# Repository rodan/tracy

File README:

gps tracker based on a MSP430F5510 uC with a gprs connection for reporting and command input.

 source:       https://github.com/rodan/tracy 
 author:       Petre Rodan <2b4eda@subdimension.ro>
 license:      GNU GPLv3

Features:
 - both hardware and software are opensource
 - an f-ram chip for input data buffering
 - resilient software architecture
 - all gps/gsm operations controlled by timer interrupts which allows control of both sub-systems in the same time
 - great flexibility given by configuration variables

 prototype pictures available here:  https://photos.app.goo.gl/5ZgdGM5Km6QHHfX5A
 documentation available here:       https://github.com/rodan/tracy/blob/master/doc/tracy_manual.pdf

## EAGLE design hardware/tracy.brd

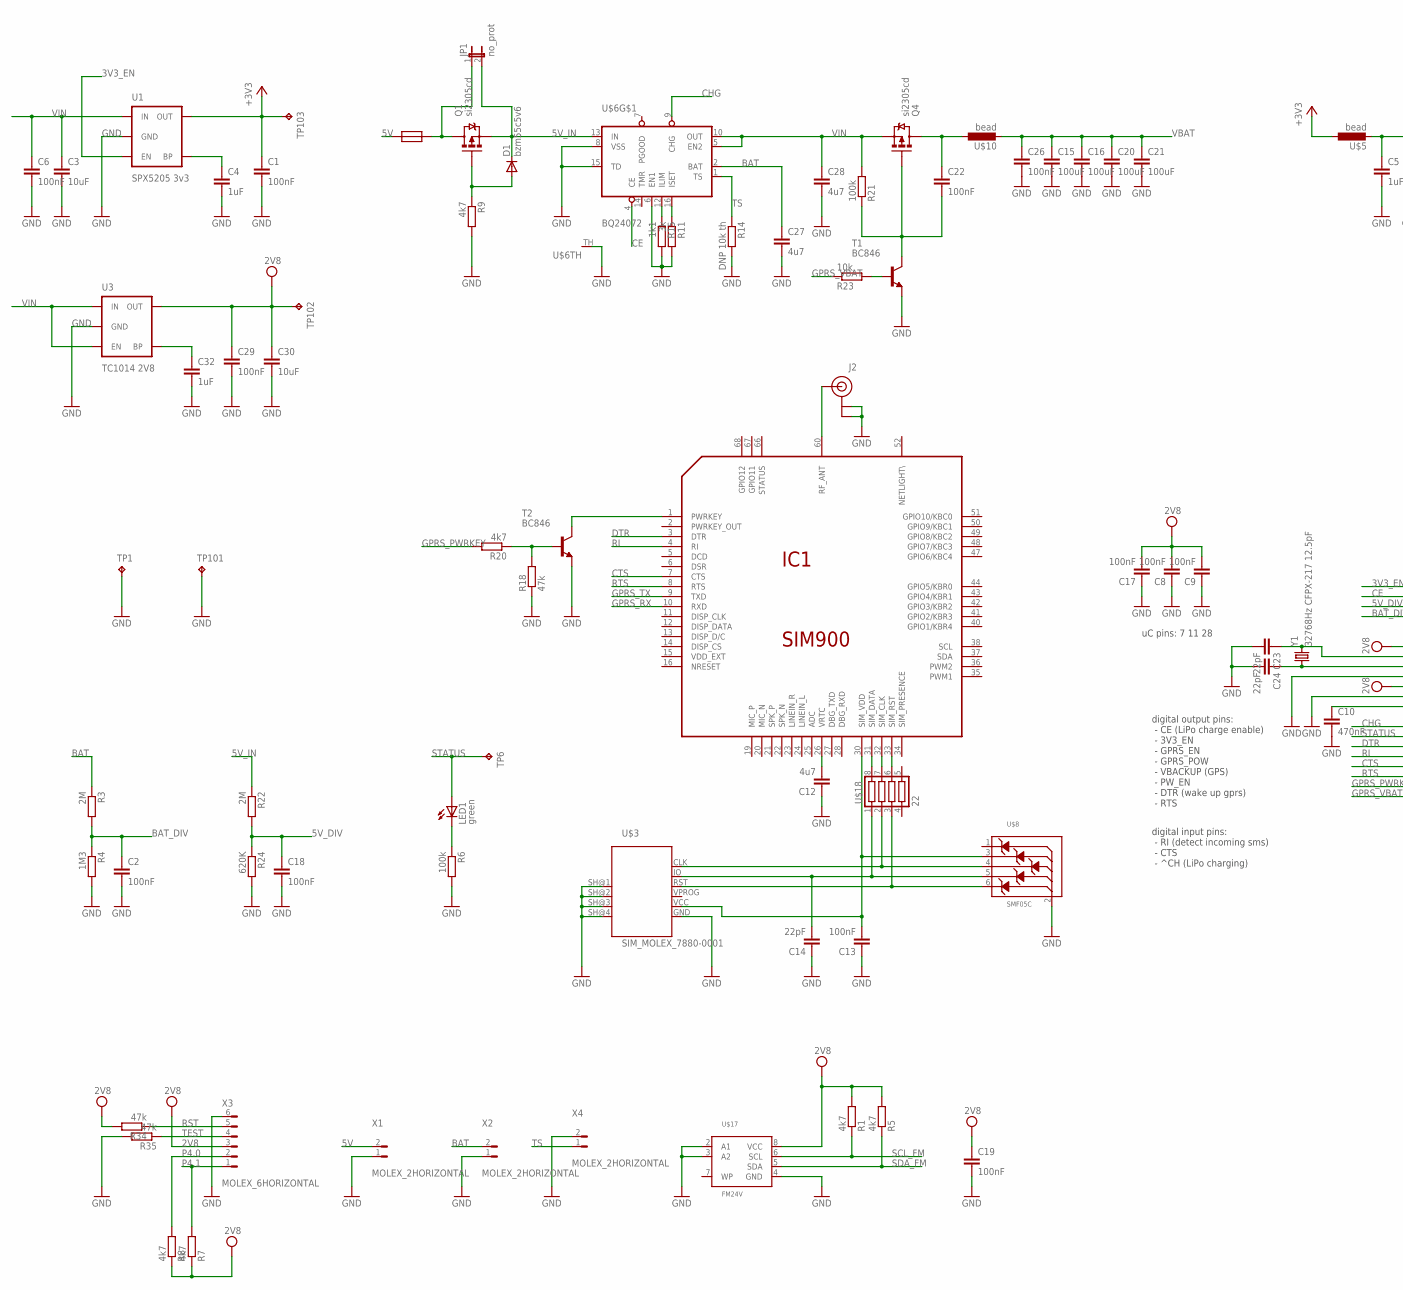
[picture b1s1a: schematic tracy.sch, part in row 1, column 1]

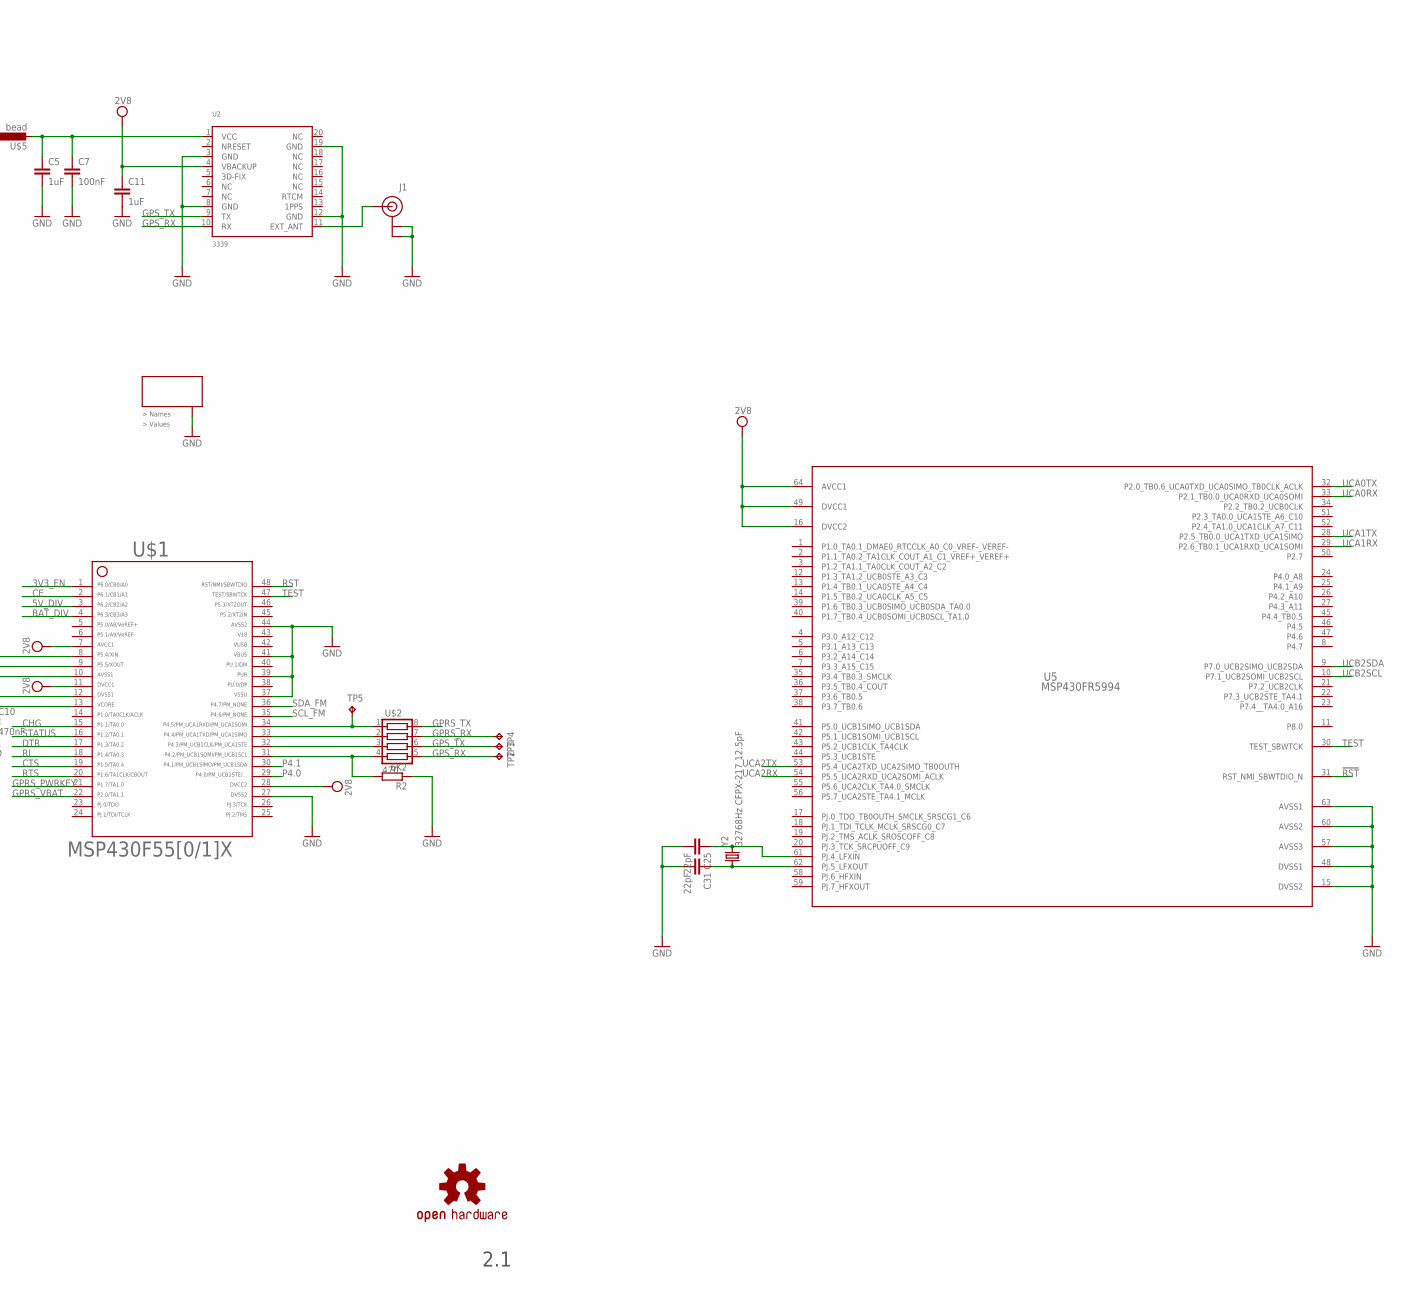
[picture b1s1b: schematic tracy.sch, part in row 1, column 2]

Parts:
C1, C2, C6, C7, C8, C9, C13, C17, C18, C19, C22, C26, C29: 100nF; C0805
C3: 10uF; C0805
C4, C5, C11, C32: 1uF; C0805
C10: 470nF; C0805
C12: 4u7; C0805
C14, C23, C24, C25, C31: 22pF; C0805
C15, C16, C20, C21: 100uF; C1206
C27, C28: 4u7; C1206
C30: 10uF; C1206
D1: bzm55c5v6; MICROMELF-W
IC1: SIM900
J1, J2: U.FL
JP1: no_prot; SJ_2S-NO
LED1: green; CHIPLED_0805
Q1, Q4: si2305cd; SOT23-3_POWER
R1, R5, R7, R8, R9, R20: 4k7; R0805W
R2: 6K2; R0805W
R3, R22: 2M; R0805W
R4: 1M3; R0805W
R6, R21: 100k; R0805W
R11: 3k; R0805W
R14: DNP 10k th; R0805W
R15: 1k1; R0805W
R18, R34, R35: 47k; R0805W
R23: 10k; R0805W
R24: 620K; R0805W
T1, T2: BC846; SOT23
TP1, TP2, TP3, TP4, TP5, TP6, TP101, TP102, TP103: TPTP12R; TP12R
U1: SPX5205 3v3; SOT23-5
U2: 3339; FGPMMOPA6H
U3: TC1014 2V8; SOT23-5
U5: MSP430FR5994; PM0064A_N
U$1: MSP430F5510; PT48
U$2: 470; YC164
U$3: SIM_MOLEX_7880-0001; MOLEX_7880-0001
U$5, U$10: bead; L0805W
U$6: BQ24072; S-PVQFN-N16
U$7: OSHW-LOGOM; OSHW-LOGO-M
U$8: SMF05C; SC-88
U$9: RESETTABLE_0805; 0805W
U$17: FM24V; SO-08
U$18: 22; YC164
U$23: G203C
X1, X2, X4: MOLEX_2HORIZONTAL; 0530480210
X3: MOLEX_6HORIZONTAL; 0530480610
Y1, Y2: 32768Hz CFPX-217 12.5pF; CRYSTAL-SMD-3.2X1.5

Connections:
2V8: C8.2, C9.2, C11.1, C17.2, C19.1, C29.1, C30.1, R1.2, R5.2, R7.1, R8.1, R34.2, TP102.TP, U2.4 (VBACKUP), U3.5 (OUT), U5.16 (DVCC2), U5.49 (DVCC1), U5.64 (AVCC1), U$1.7, U$1.11, U$1.28, U$17.8 (VCC), X3.3 (4)
3V3_EN: U1.3 (EN), U$1.1
5V: U$9.1, X1.2 (1)
5V_DIV: C18.1, R22.2, R24.1, U$1.3
5V_IN: D1.C, JP1.2, Q1.2 (S), R22.1, U$6.13 (IN)
42: U$1.42
43: U$1.43
46: U$1.46
!RST: U5.31 (RST_NMI_SBWTDIO_N)
+3V3: C1.1, TP103.TP, U1.5 (OUT), U$5.1
BAT: C27.1, R3.1, U$6.2 (BAT), X2.2 (1)
BAT_DIV: C2.1, R3.2, R4.1, U$1.4
CE: U$1.2, U$6.4 (CE)
CHG: U$1.15, U$6.9 (CHG)
CTS: IC1.7 (CTS), U$1.19
DTR: IC1.3 (DTR), U$1.17
GND: C1.2, C2.2, C3.2, C4.2, C5.2, C6.2, C7.2, C8.1, C9.1, C10.2, C11.2, C12.1, C13.1, C14.1, C15.2, C16.2, C17.1, C18.2, C19.2, C20.2, C21.2, C23.2, C24.2, C25.2, C26.2, C27.2, C28.2, C29.2, C30.2, C31.2, C32.2, IC1.17 (GND), IC1.18 (GND), IC1.29 (GND), IC1.39 (GND), IC1.45 (GND), IC1.46 (GND), IC1.53 (GND), IC1.54 (GND), IC1.58 (GND), IC1.59 (GND), IC1.61 (GND), IC1.62 (GND), IC1.63 (GND), IC1.64 (GND), IC1.65 (GND), J1.P$1 (GND), J1.P$2 (GND), J2.P$1 (GND), J2.P$2 (GND), R2.1, R4.2, R6.2, R9.2, R11.2, R14.2, R15.2, R18.1, R24.2, R35.2, T1.2 (E), T2.2 (E), TP1.TP, TP101.TP, U1.2 (GND), U2.3 (GND), U2.8 (GND), U2.12 (GND), U2.19 (GND), U3.2 (GND), U5.15 (DVSS2), U5.48 (DVSS1), U5.57 (AVSS3), U5.60 (AVSS2), U5.63 (AVSS1), U$1.10, U$1.12, U$1.27, U$1.37, U$1.39, U$1.41, U$1.44, U$3.GND, U$3.SH@1 (SH), U$3.SH@2 (SH), U$3.SH@3 (SH), U$3.SH@4 (SH), U$6.6 (EN1), U$6.8 (VSS), U$6.15 (TD), U$6.TH, U$8.2 (ANODE), U$17.2 (A1), U$17.3 (A2), U$17.4 (GND), U$23.SH@1, U$23.SH@2, U$23.SH@3, U$23.SH@4, X1.1 (2), X2.1 (2), X3.6 (1), X4.2 (1)
GPRS_PWRKEY: R20.2, U$1.21
GPRS_RX: IC1.10 (RXD), TP4.TP, U$2.7
GPRS_TX: IC1.9 (TXD), U$2.8
GPRS_VBAT: R23.1, U$1.22
GPS_RX: TP2.TP, U2.10 (RX), U$2.5
GPS_TX: TP3.TP, U2.9 (TX), U$2.6
GPS_VCC: C5.1, C7.1, U2.1 (VCC), U$5.2
unnamed: U$1.32, U$2.3
unnamed: C4.1, U1.4 (BP)
unnamed: R2.2, U$1.31, U$2.4
unnamed: U$1.33, U$2.2
unnamed: JP1.1, Q1.3 (D), U$9.2
unnamed: C10.1, U$1.13
unnamed: R23.2, T1.1 (B)
unnamed: LED1.C, R6.1
unnamed: J1.P$3 (SIGNAL), U2.11 (EXT_ANT)
unnamed: TP5.TP, U$1.34, U$2.1
unnamed: D1.A, Q1.1 (G), R9.1
unnamed: C31.1, U5.62 (PJ.5_LFXOUT), Y2.P$1 (1)
unnamed: C25.1, U5.61 (PJ.4_LFXIN), Y2.P$2 (2)
unnamed: IC1.31 (SIM_DATA), U$18.8
unnamed: IC1.32 (SIM_CLK), U$18.7
unnamed: IC1.33 (SIM_RST), U$18.6
unnamed: C24.1, U$1.9, Y1.P$1 (1)
unnamed: C23.1, U$1.8, Y1.P$2 (2)
unnamed: R11.1, U$6.16 (ISET)
unnamed: R15.1, U$6.12 (ILIM)
unnamed: R18.2, R20.1, T2.1 (B)
unnamed: IC1.60 (RF_ANT), J2.P$3 (SIGNAL)
unnamed: C22.2, Q4.1 (G), R21.1, T1.3 (C)
unnamed: C22.1, Q4.3 (D), U$10.1
unnamed: C32.1, U3.4 (BP)
P4.0: R8.2, U$1.29, X3.2 (5)
P4.1: R7.2, U$1.30, X3.1 (6)
PWRKEY: IC1.1 (PWRKEY), T2.3 (C)
RI: IC1.4 (RI), U$1.18
RST: R34.1, U$1.48, X3.5 (2)
RTS: IC1.8 (RTS), U$1.20
SCL_FM: R1.1, U$1.35, U$17.6 (SCL)
SDA_FM: R5.1, U$1.36, U$17.5 (SDA)
SIMLOCK_CLK: U$3.CLK, U$8.4 (CATODE3), U$18.2
SIMLOCK_IO: C14.2, U$3.IO, U$8.5 (CATODE4), U$18.1
SIMLOCK_RST: U$3.RST, U$8.6 (CATODE5), U$18.3
SIM_VCC: C13.2, IC1.30 (SIM_VDD), U$3.VCC, U$8.3 (CATODE2)
STATUS: LED1.A, TP6.TP, U$1.16
TEST: R35.1, U5.30 (TEST_SBWTCK), U$1.47, X3.4 (3)
TS: R14.1, U$6.1 (TS), X4.1 (2)
UCA0RX: U5.33 (P2.1_TB0.0_UCA0RXD_UCA0SOMI)
UCA0TX: U5.32 (P2.0_TB0.6_UCA0TXD_UCA0SIMO_TB0CLK_ACLK)
UCA1RX: U5.29 (P2.6_TB0.1_UCA1RXD_UCA1SOMI)
UCA1TX: U5.28 (P2.5_TB0.0_UCA1TXD_UCA1SIMO)
UCA2RX: U5.54 (P5.5_UCA2RXD_UCA2SOMI_ACLK)
UCA2TX: U5.53 (P5.4_UCA2TXD_UCA2SIMO_TB0OUTH)
UCB2SCL: U5.10 (P7.1_UCB2SOMI_UCB2SCL)
UCB2SDA: U5.9 (P7.0_UCB2SIMO_UCB2SDA)
VBAT: C15.1, C16.1, C20.1, C21.1, C26.1, IC1.55 (VBAT), IC1.56 (VBAT), IC1.57 (VBAT), U$10.2
VIN: C3.1, C6.1, C28.1, Q4.2 (S), R21.2, U1.1 (IN), U3.1 (IN), U3.3 (EN), U$6.5 (EN2), U$6.10 (OUT)
VRTC: C12.2, IC1.26 (VRTC)

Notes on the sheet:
2.1
uC pins: 7 11 28
digital output pins: - CE (LiPo charge enable) - 3V3_EN - GPRS_EN - GPRS_POW - VBACKUP (GPS) - PW_EN - DTR (wake up gprs) - RTS
digital input pins: - RI (detect incoming sms) - CTS - ^CH (LiPo charging)

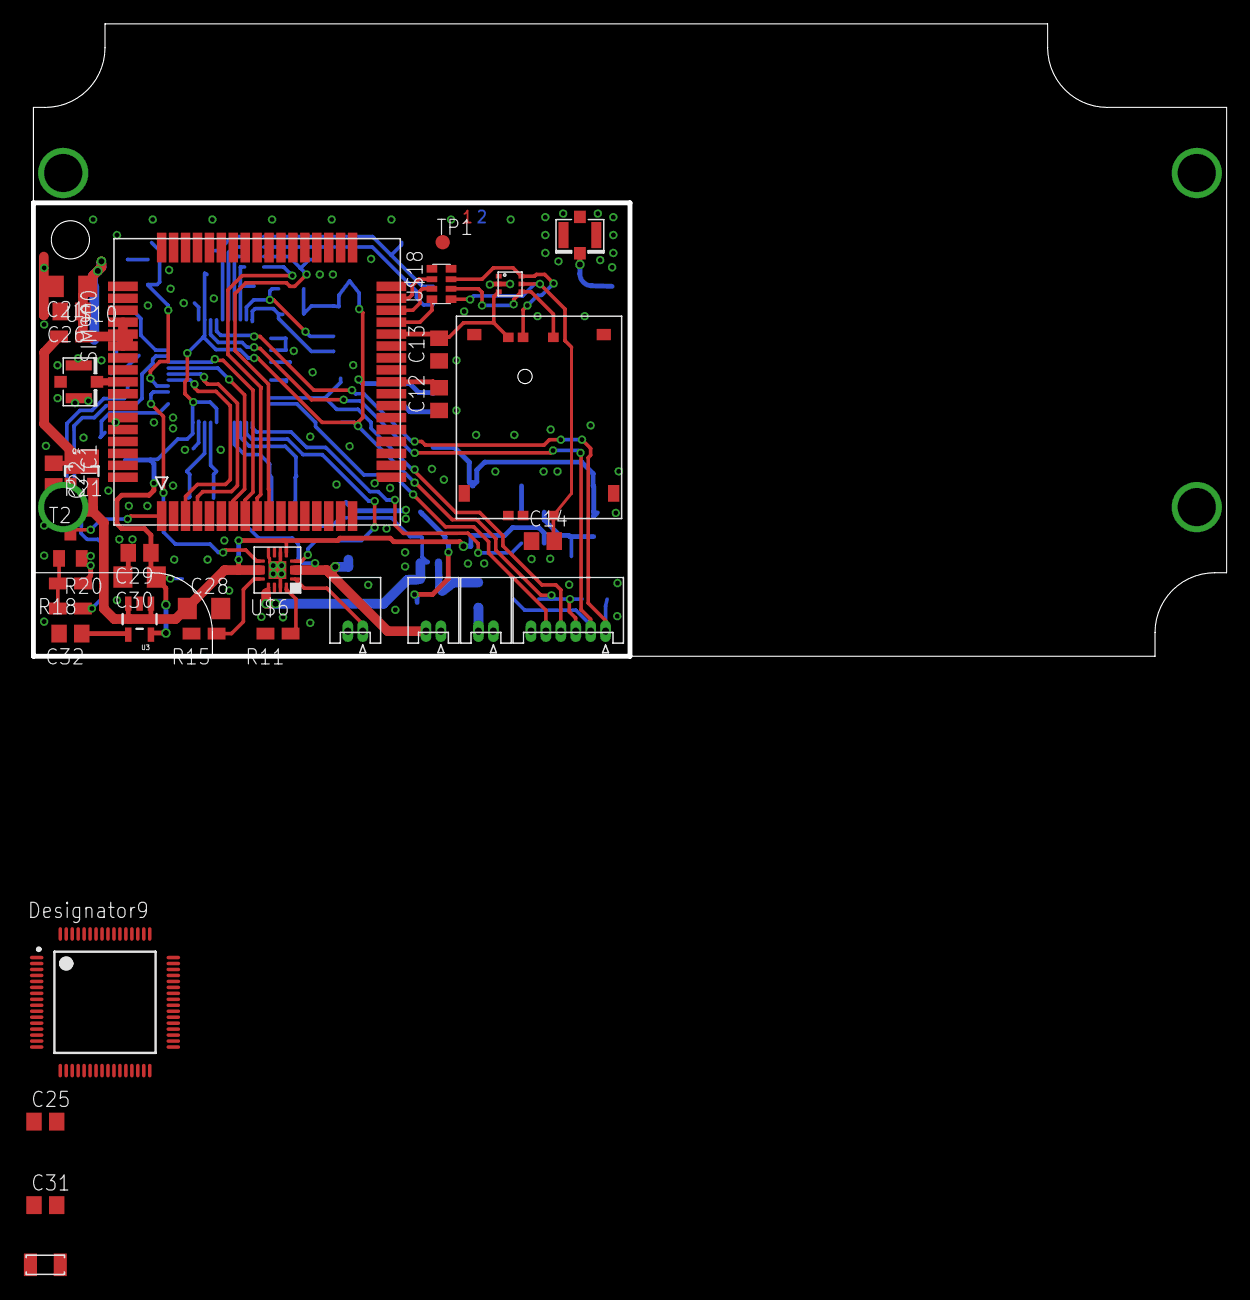
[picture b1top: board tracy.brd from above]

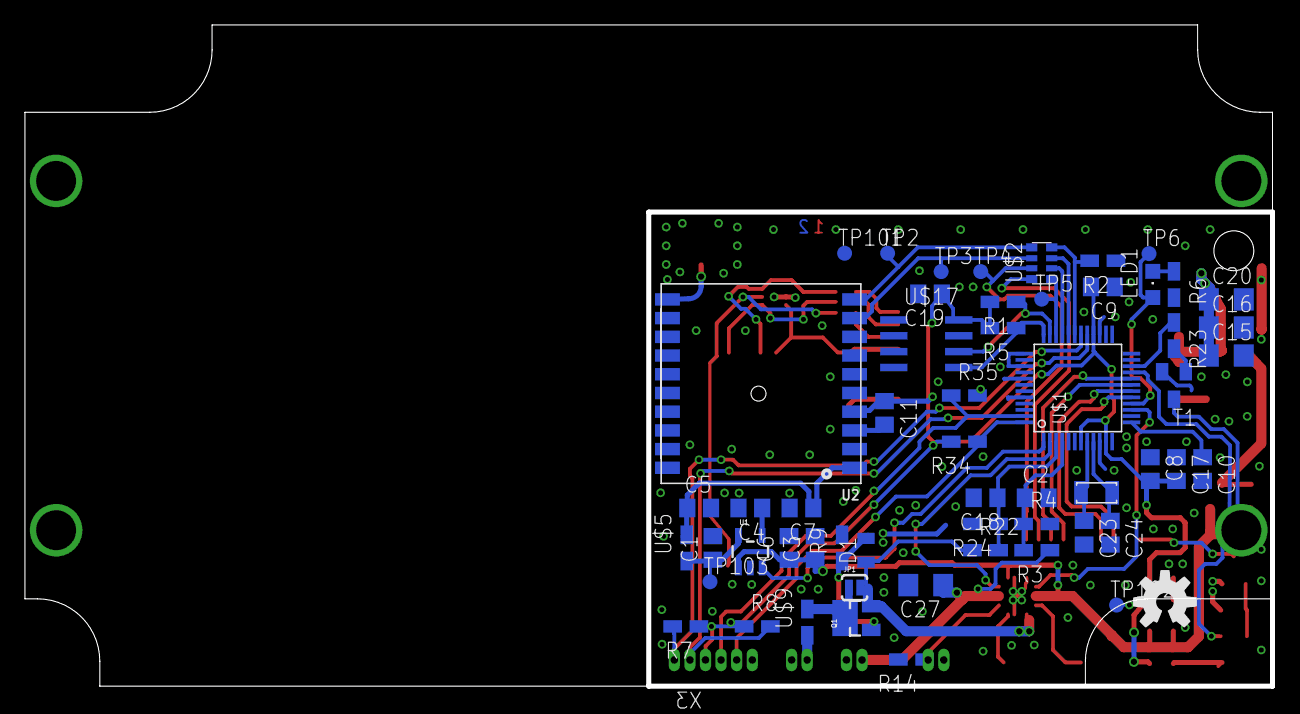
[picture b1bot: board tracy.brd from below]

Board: 2 copper layers, 100.0 x 53.0 mm, 93 parts (57 on the bottom side), 63 nets.

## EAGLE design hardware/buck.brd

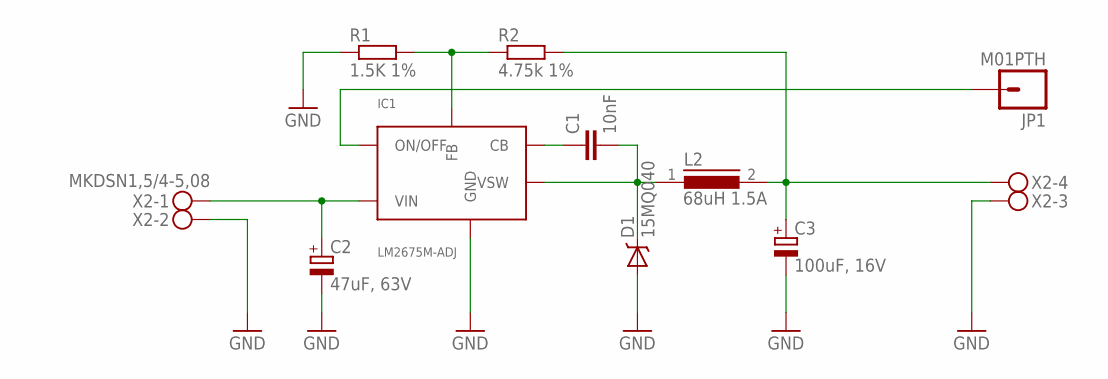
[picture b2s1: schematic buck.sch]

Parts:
C1: 10nF; C0805
C2: 47uF, 63V; PANASONIC_F
C3: 100uF, 16V; PANASONIC_D
D1: 15MQ040; SMA-DIODE
IC1: LM2675M-ADJ; SO-08
JP1: M01PTH; 1X01
L2: 68uH 1.5A; DR125
R1: 1.5K 1%; R0805W
R2: 4.75k 1%; R0805W
X2: MKDSN1,5/4-5,08

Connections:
GND: C2.-, C3.-, D1.A, IC1.6 (GND), R1.1, X2.2, X2.3
unnamed: IC1.4 (FB), R1.2, R2.1
unnamed: C1.2, D1.C, IC1.8 (VSW), L2.1
unnamed: C1.1, IC1.1 (CB)
unnamed: C3.+, L2.2, R2.2, X2.4
unnamed: IC1.5 (ON/OFF), JP1.1
unnamed: C2.+, IC1.7 (VIN), X2.1

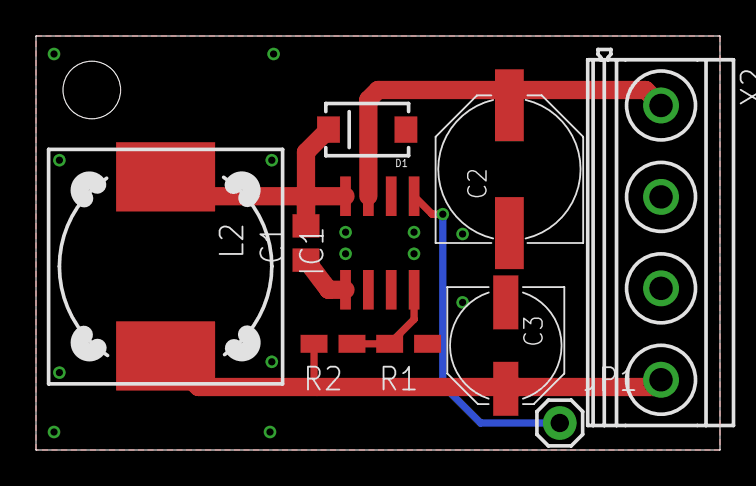
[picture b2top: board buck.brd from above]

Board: 2 copper layers, 38.0 x 23.0 mm, 10 parts (0 on the bottom side), 7 nets.

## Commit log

2013-11-03 nmea parsing tests
2013-11-04 parse pipes
2013-11-10 add firmware
2013-11-10 add uart RX capability
2013-11-10 move buffer into IRQ
2013-11-24 fix ADC REFVSEL bug
2013-11-24 use reference libs
2013-12-06 create sim card reader footprint
2013-12-10 sch work
2013-12-14 daily snapshot
2014-01-04 pcb done
2014-01-07 add silkscreen
2014-01-27 remove python scripts
2014-05-12 checks
2014-06-30 tweaks
2014-07-06 add nmea parser driver
2014-07-06 remove craft
2014-07-06 daily
2014-07-06 add returns in parse_gps
2014-07-11 test gprs part1
2014-07-17 sim900 replies at last
2014-07-17 add console buffer timeout
2014-07-17 shorten delay until uart1_rx_event is picked up
2014-07-18 add sim900 first pwron function
2014-07-18 autodetect factory settings, set new defaults into sim900
2014-07-19 activate flow control
2014-07-19 sim900 halt function - part1
2014-07-22 add bat voltage check
2014-07-22 add sms sending
2014-07-23 add /8 divider to timer_A0
2014-07-23 add gprs state machine
2014-07-24 add server-side parser
2014-07-24 get imei function
2014-07-28 fix http reply detection
2014-07-28 implement tasks
2014-07-30 better buffer termination
2014-07-30 add subtask queue
2014-07-31 sms parsing part1
2014-07-31 slight cleanup
2014-07-31 README fixes
2014-08-01 add server side README
2014-08-01 add checks for pin_rdy, ip_start
2014-08-01 task queue redesign
2014-08-02 fix sms auth
2014-08-05 keepout under fuse
2014-08-06 set text mode before sms listing
2014-08-07 first tests
2014-08-08 parse CENG lists, part1
2014-08-09 get tower data
2014-08-09 add setup cmd
2014-08-09 add tower cell data - part 2
2014-08-09 use defines for time values
2014-08-09 use defines for time values part2
2014-08-09 make sure timers are started before sim900_tx, further divide clock by 8
2014-08-09 never block if sim900 is faulty
2014-08-21 geofence part1
2014-08-23 add fram buffer
2014-08-25 cleanup
2014-09-01 rev 2
2014-09-02 optionally send voltages
2014-09-03 geofence part 2
2014-09-04 add geofence test program
2014-09-04 geofence distance tests
2014-09-04 README added
2014-09-04 add buck converter board
2014-09-04 gps debug session
2014-09-05 send PDOP data
2014-09-05 use memset to reset last fix
2014-09-06 use state machine in main schedule funct
2014-09-07 test position averaging
2014-09-08 vref saved to flash
2014-09-10 POST parsing
2014-09-10 add HTTP POST method for transmitting data
2014-09-11 server-side POST
2014-09-11 save pseudocrc to db
2014-09-11 timestamp always visible even is no gps fix
2014-09-11 timestamp always visible - firmware
2014-09-11 hopefully proper gprs connection reset upon fail
2014-09-13 cell tower-based mean position
2014-09-14 send Host in POST header
2014-09-14 perl visualizer now generates google maps with positioning data
2014-09-15 CGI fixes
2014-09-15 reset sim900.err after sending it
2014-09-20 add latex documentation
2014-10-01 add support for FM24V10 f-ram
2014-10-01 add fram seek
2014-10-01 have some sleep in fm24
2014-10-02 add some delay after &v0
2014-10-02 move silkscreen labels
2014-10-03 store info into f-ram
2014-10-04 different state machines for gps/gprs measurements
2014-10-05 mem segmentation
2014-10-06 segmented send
2014-10-07 getting there
2014-10-07 server scripts now support multiple subpacket POSTs
2014-10-07 fix loop
2014-10-07 fix loop part2
2014-10-07 pdop reset rewrite
2014-10-09 fm24 write check and sleep mode
2014-10-09 set up timings via sms
2014-10-09 add geofence_trigger to the settings struct
2014-10-10 rename period->interval, add ping cmd, add static/moving tx_intervals
2014-10-11 add set factory defaults command
2014-10-11 small cleanup
2014-10-14 doc update
2014-10-14 manual update
2014-10-16 70uA sleep instead of 600uA
2014-10-16 fill up currents in manual
2014-10-17 fix 4 char sms commands
2014-10-18 fix reset to defaults sms tx
2014-10-29 add fm24 memtest routine
2014-10-29 add tool that reads the fm24 contents into a file
2014-11-08 add delay after SIM900_OFF
2014-11-09 remove REV1 ifdefs, add blackout intervals
2014-11-18 nicer qa interface
2014-11-18 add flash clear function
2014-11-28 increase MAX_SEG for FM24CL64B
2014-11-28 update geofence_test
2014-11-28 remove adc calibration
2014-12-10 controlled charging
2014-12-18 read adc during pkt store
2015-03-28 cleanup README
2015-04-02 add rowno argument
2015-04-02 if cell_id == 0 ignore coordinates
2015-08-27 battery charge condition changed
2015-09-10 latest
2018-09-01 email change
2018-12-04 add pdf manual
2018-12-06 compatibility with latest latex
2018-12-06 add flash store in qa console
2018-12-07 longer failure blackout intervals
2018-12-13 update documentroot files
2018-12-21 set output levels before direction
2019-08-23 update links
2019-08-25 replace snprintfs
2019-09-11 rev3 - initial switch to msp430fr5994

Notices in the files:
parts and their libraries:
SparkFun-DiscreteSemi: Licensing: Creative Commons ShareAlike 4.0 International - https://creativecommons.org/licenses/by-sa/4.0
SparkFun-Connectors: Licensing: CC v3.0 Share-Alike You are welcome to use this library for commercial purposes.
